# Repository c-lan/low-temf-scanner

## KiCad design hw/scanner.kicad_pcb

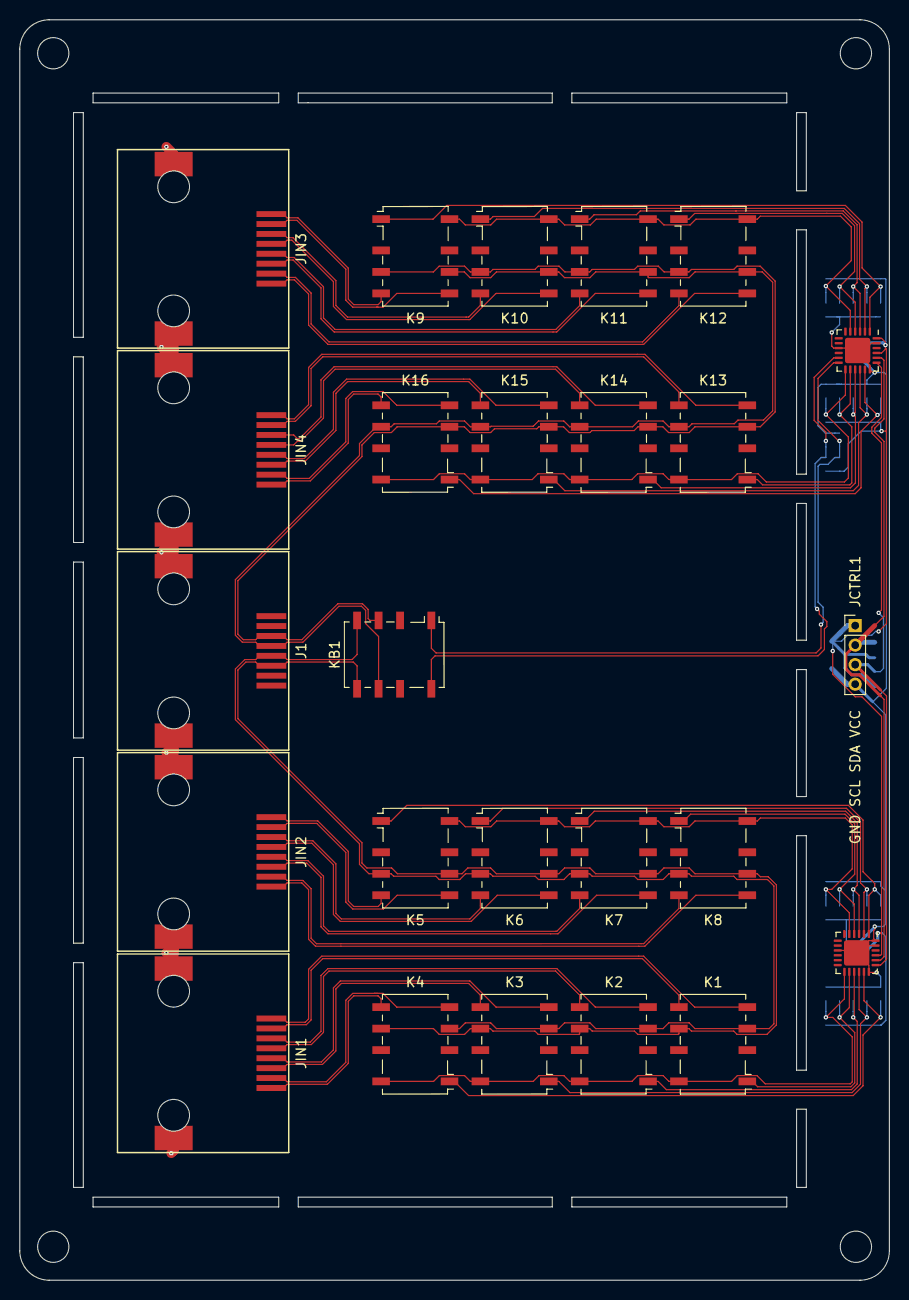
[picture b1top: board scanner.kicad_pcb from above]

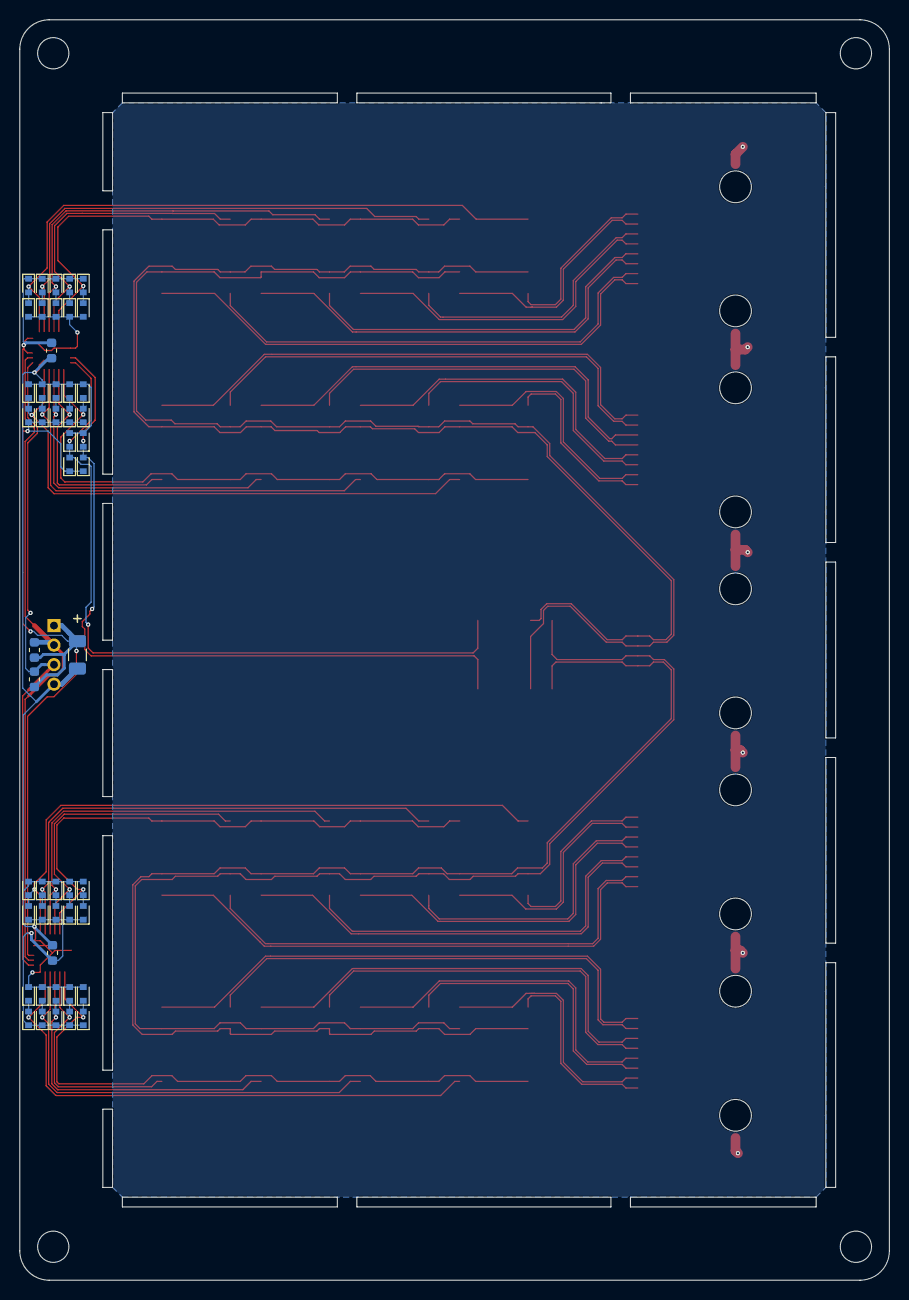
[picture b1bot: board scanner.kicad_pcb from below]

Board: 2 copper layers, 89.0 x 129.0 mm, 78 parts (49 on the bottom side), 63 nets.

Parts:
C1, C2: 100n; C_0603_1608Metric
C3: 15u; C_1206_3216Metric
D1, D2, D3, D4, D5, D6, D7, D8, D9, D10, D11, D12, D13, D14, D15, D16, D17, D18, D19, D20, D21, D22, D23, D24, D25, D26, D27, D28, D29, D30, D31, D32, D33, D34, D35, D36, D37, D38, D39, D40, D41, D42, D43, D44: D_Small; D_SOD-523
H1, H2, H3, H4: MountingHole; MountingHole_3.2mm_M3
J1: 6339160-1
JCTRL1: Conn_01x04; PinHeader_1x04_P2.00mm_Vertical
JIN1, JIN2, JIN3, JIN4: 6339160-1
K1, K2, K3, K4, K5, K6, K7, K8, K9, K10, K11, K12, K13, K14, K15, K16: G6KU-2; Relay_DPDT_Omron_G6K-2F-Y
KB1: G6KU-2; Relay_DPDT_Omron_G6K-2F-Y
R1, R2: 100k; R_0603_1608Metric
U1, U2: TCA9535RTWR; QFN-24-1EP_4x4mm_P0.5mm_EP2.6x2.6mm

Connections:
+3V3: C1.1, C2.1, C3.1, D1.1, D3.1, D5.1, D7.1, D9.1, D11.1, D13.1, D15.1, D17.1, D19.1, D21.1, D23.1, D25.1, D27.1, D29.1, D31.1, D33.1, D35.1, D37.1, D39.1, D41.1, D43.1, JCTRL1.1, R1.1, R2.1, U1.21, U1.24, U2.21
/CHA_COM1: D39.2, D40.1, K1.8, K2.8, K3.8, K4.8, U2.13
/CHA_COM2: D19.2, D20.1, K5.8, K6.8, K7.8, K8.8, U2.5
/CHA_N: J1.4, K1.3, K2.3, K3.3, K4.3, K5.3, K6.3, K7.3, K8.3, KB1.4
/CHA_P: J1.3, K1.6, K2.6, K3.6, K4.6, K5.6, K6.6, K7.6, K8.6, KB1.5
/CHB_COM1: D37.2, D38.1, K9.8, K10.8, K11.8, K12.8, U1.5
/CHB_COM2: D17.2, D18.1, K13.8, K14.8, K15.8, K16.8, U1.13
/CHB_N: J1.6, K9.3, K10.3, K11.3, K12.3, K13.3, K14.3, K15.3, K16.3, KB1.3
/CHB_P: J1.5, K9.6, K10.6, K11.6, K12.6, K13.6, K14.6, K15.6, K16.6, KB1.6
/SCL: JCTRL1.3, R2.2, U1.19, U2.19
/SDA: JCTRL1.2, R1.2, U1.20, U2.20
/SW0: D35.2, D36.1, K4.1, U2.17
/SW1: D31.2, D32.1, K3.1, U2.16
/SW2: D27.2, D28.1, K2.1, U2.15
/SW3: D23.2, D24.1, K1.1, U2.14
/SW4: D15.2, D16.1, K8.1, U2.4
/SW5: D11.2, D12.1, K7.1, U2.3
/SW6: D7.2, D8.1, K6.1, U2.2
/SW7: D3.2, D4.1, K5.1, U2.1
/SW8: D13.2, D14.1, K12.1, U1.4
/SW9: D9.2, D10.1, K11.1, U1.3
/SW10: D5.2, D6.1, K10.1, U1.2
/SW11: D1.2, D2.1, K9.1, U1.1
/SW12: D33.2, D34.1, K16.1, U1.17
/SW13: D29.2, D30.1, K15.1, U1.16
/SW14: D25.2, D26.1, K14.1, U1.15
/SW15: D21.2, D22.1, K13.1, U1.14
/SWCOMB: D43.2, D44.1, KB1.1, U1.12
/SWCOMB_COM: D41.2, D42.1, KB1.8, U1.11
/cha_0_3/CH0_N: JIN1.2, K4.4
/cha_0_3/CH0_P: JIN1.1, K4.5
/cha_0_3/CH1_N: JIN1.4, K3.4
/cha_0_3/CH1_P: JIN1.3, K3.5
/cha_0_3/CH2_N: JIN1.6, K2.4
/cha_0_3/CH2_P: JIN1.5, K2.5
/cha_0_3/CH3_N: JIN1.8, K1.4
/cha_0_3/CH3_P: JIN1.7, K1.5
/cha_4_7/CH0_N: JIN2.2, K8.4
/cha_4_7/CH0_P: JIN2.1, K8.5
/cha_4_7/CH1_N: JIN2.4, K7.4
/cha_4_7/CH1_P: JIN2.3, K7.5
/cha_4_7/CH2_N: JIN2.6, K6.4
/cha_4_7/CH2_P: JIN2.5, K6.5
/cha_4_7/CH3_N: JIN2.8, K5.4
/cha_4_7/CH3_P: JIN2.7, K5.5
/chb_0_3/CH0_N: JIN3.2, K12.4
/chb_0_3/CH0_P: JIN3.1, K12.5
/chb_0_3/CH1_N: JIN3.4, K11.4
/chb_0_3/CH1_P: JIN3.3, K11.5
/chb_0_3/CH2_N: JIN3.6, K10.4
/chb_0_3/CH2_P: JIN3.5, K10.5
/chb_0_3/CH3_N: JIN3.8, K9.4
/chb_0_3/CH3_P: JIN3.7, K9.5
/chb_4_7/CH0_N: JIN4.2, K16.4
/chb_4_7/CH0_P: JIN4.1, K16.5
/chb_4_7/CH1_N: JIN4.4, K15.4
/chb_4_7/CH1_P: JIN4.3, K15.5
/chb_4_7/CH2_N: JIN4.6, K14.4
/chb_4_7/CH2_P: JIN4.5, K14.5
/chb_4_7/CH3_N: JIN4.8, K13.4
/chb_4_7/CH3_P: JIN4.7, K13.5
GNDA: J1.SH, JIN1.SH, JIN2.SH, JIN3.SH, JIN4.SH
GNDD: C1.2, C2.2, C3.2, D2.2, D4.2, D6.2, D8.2, D10.2, D12.2, D14.2, D16.2, D18.2, D20.2, D22.2, D24.2, D26.2, D28.2, D30.2, D32.2, D34.2, D36.2, D38.2, D40.2, D42.2, D44.2, JCTRL1.4, U1.9, U1.18, U1.23, U1.25, U2.9, U2.18, U2.23, U2.24, U2.25

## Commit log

2021-02-07 Add basic software
